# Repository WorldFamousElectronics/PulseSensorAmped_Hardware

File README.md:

# PulseSesorAmped_Hardware
These files were created in [Design Spark](http://www.designspark.com/) Schematic Layout and PCB Capture Software 

You will need to copy the contents of DesignSparkLibraryFiles into the default Library that Design Spark uses. Normally something like 

`Documents\DesignSpark PCB\Library`

This is the only way you will be able to use or modify the APDS-9008 part or the reverse mount LED part.

CONTRIBUTORS BACKTRACK AND NOTIFICATION

joel@pulsesensor.com
yury@pulsesensor.com

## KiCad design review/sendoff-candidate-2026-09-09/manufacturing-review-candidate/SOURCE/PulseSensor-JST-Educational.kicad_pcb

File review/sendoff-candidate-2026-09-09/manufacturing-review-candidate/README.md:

# PulseSensor JST educational board — review candidate

DEVELOPMENT • 2026-09-09 • PulseSilverBookPro

This is a concrete native CAD and manufacturing-export candidate, not an approved production release. No supplier upload or order has been made.

## Design

15.875 mm circular board, 1.6 mm thick. Black solder mask, white silkscreen on both sides. User-facing optical front is KiCad B side; circuit back is KiCad F side. D1, U1, J1 and board outline are unchanged. Twelve passive/diode parts were rearranged and copper rerouted; all original pin-to-net connections and local pad geometries are preserved.

The front uses a photo-reconstructed heart and curved pulsesensor.com wordmark. It is not verified against an original historical artwork master. Back lettering identifies parts and functional groups; dotted guides describe signal connections with deliberate gaps at crossings and text. They are explanatory ink, not a complete depiction of copper or current flow. The solid arrow describes conventional current on the LED cathode-to-resistor branch. Capacitors do not carry steady DC through their dielectric. The full component-function key is in the review page.

## Evidence

All 16 geometry/electrical comparison checks passed: zero unconnected nets, zero schematic parity issues, ERC clear, fixed optics preserved, correct 16-component placement export and unchanged controlled component selections. Native candidate SHA-256: 035ff099151d272f77bd0d54e158b8264b486bc1b7c166ecc0c92d3a766d4b6a.

DRC retains one original D1 optical NPTH / U1 courtyard exception. No new DRC warnings. Measured silk-to-opening clearance is at least 0.1536 mm on F and 0.1584 mm on B. Lettering targets 0.8 mm height and 0.15 mm strokes; full glyph stem metrology and supplier print reconciliation remain to be completed. See VALIDATION.

## Manufacturing review notes / hold points

- This package is on HOLD for release. Existing optical courtyard exception needs the formal review/waiver required by the hardware workflow.
- D1, D2 and U1 source models are mesh-only; verified STEP-capable models and independent mechanical inspection remain outstanding. Rendered component bodies are illustrative and do not constitute mechanical proof.
- Ten populated views are supplied. KiCad renders can display via holes/rings despite native tenting flags. Fabrication mask data and supplier tenting capability govern actual appearance; verify tenting for the 0.30 mm drills.
- Gerbers, drill and CPL share the original auxiliary origin (92.0625, 107.9375). CPL uses the native KiCad side/rotation convention. Confirm the supplier’s assembly interpretation before release.
- The controlled BOM and population matrix are byte-for-byte copies of the original submitted selections. Their original lot quantities/identifiers are provenance, not authorization for a new order. Reconcile the new lot explicitly before ordering.
- Human Gerber and assembly review, required repeat-build evidence, fabricator reconciliation and CEO release approval remain pending. This rearranged layout has not been bench validated.

## Provenance

Submitted source archive SHA-256: 0afda167b52ab0b0251cf22f91fd92fefa5dcf5e74f67b36446e7ec775acf792.
Submitted native PCB SHA-256: b439dcff82c4553731ac35ebcd27276899f8dfbbfcd35f2351d8101497eb4ad4.
Source: PulseSensor-Amped-B-PCBWay-EVT-RC3-R1-FINAL / SOURCE_SUPPORT / PulseSensor-Amped-B-JST.kicad_pcb.

Python crash dialogs were traced to KiCad pcbnew helper shutdown. Final metadata edits used standard Python text parsing and KiCad CLI checks/exports; the crash-prone helpers are no longer used.

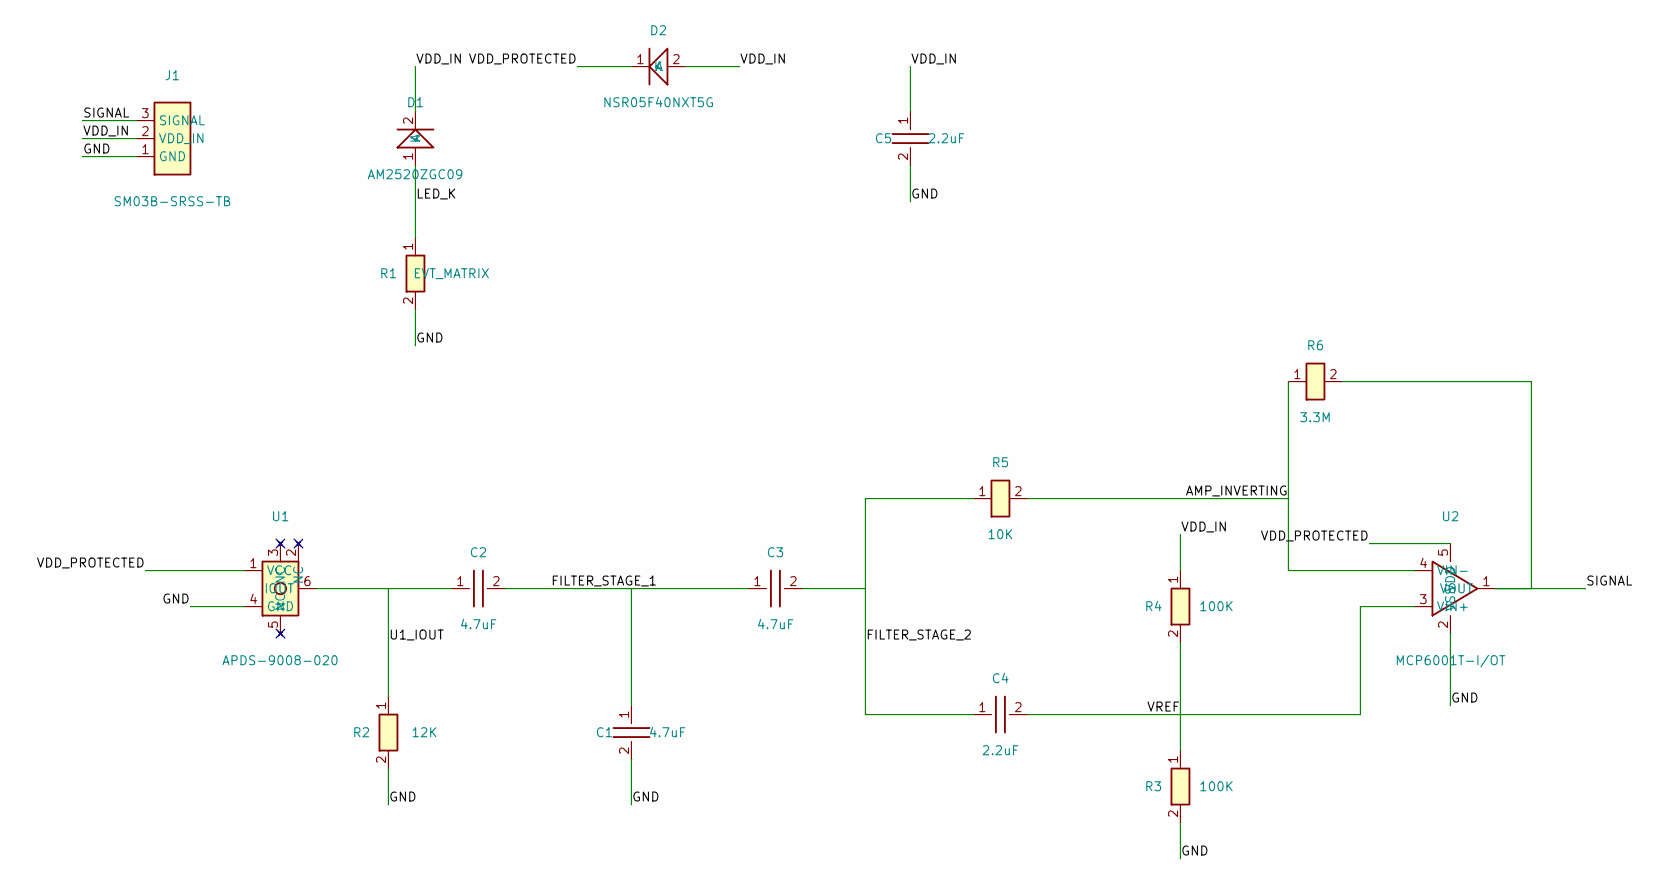
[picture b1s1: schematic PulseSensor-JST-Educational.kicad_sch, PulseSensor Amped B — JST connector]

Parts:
C1, C2, C3: 4.7uF; C_0402_Educational; MPN GRM155R60J475ME47D
C4, C5: 2.2uF; C_0402_Educational; MPN GRM155R61A225KE01D
D1: AM2520ZGC09; AM2520ZGC09_ReverseMount_OriginalAperture; MPN AM2520ZGC09
D2: NSR05F40NXT5G; NSR05F40NXT5G_DSN2; MPN NSR05F40NXT5G
J1: SM03B-SRSS-TB; JST_SH_SM03B-SRSS-TB_1x03-1MP_P1.00mm_Horizontal; MPN SM03B-SRSS-TB
R1: EVT_MATRIX; R_0402_Educational; MPN SEE_R1_SCREENING_MATRIX
R2: 12K; R_0402_Educational; MPN RC0402FR-0712KL
R3, R4: 100K; R_0402_Educational; MPN RC0402FR-07100KL
R5: 10K; R_0402_Educational; MPN RC0402FR-0710KL
R6: 3.3M; R_0402_Educational; MPN RC0402FR-073M3L
U1: APDS-9008-020; MPN APDS-9008-020
U2: MCP6001T-I/OT; SOT-23-5; MPN MCP6001T-I/OT

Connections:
/AMP_INVERTING: R5.2, R6.1, U2.4 (VIN-)
/FILTER_STAGE_1: C1.1, C2.2, C3.1
/FILTER_STAGE_2: C3.2, C4.1, R5.1
/GND: C1.2, C5.2, J1.1 (GND), R1.2, R2.2, R3.2, U1.4 (GND), U2.2 (VSS)
/LED_K: D1.1 (K), R1.1
/SIGNAL: J1.3 (SIGNAL), R6.2, U2.1 (VOUT)
/U1_IOUT: C2.1, R2.1, U1.6 (IOUT)
/VDD_IN: C5.1, D1.2 (A), D2.2 (A), J1.2 (VDD_IN), R4.1
/VDD_PROTECTED: D2.1 (K), U1.1 (VCC), U2.5 (VDD)
/VREF: C4.2, R3.1, R4.2, U2.3 (VIN+)

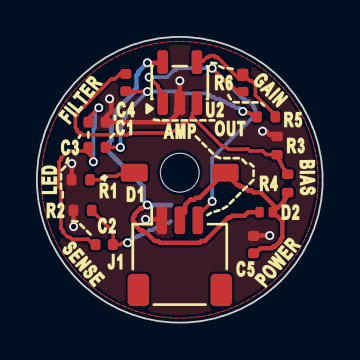
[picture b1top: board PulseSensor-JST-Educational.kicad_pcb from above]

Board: 2 copper layers, 15.9 x 15.9 mm, 16 parts (1 on the bottom side), 10 nets.

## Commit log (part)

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2016-07-27 Uploaded Hardware Design files
2017-08-30 Update License And Verify Files
2017-08-31 Updated .pcb file
    The previous .pcb file had extraneous text on it.
2018-02-27 Added Datasheet
2018-02-27 Added OSHWA Certification mark to datasheet
2025-12-01 Update gerber files in the Plots folder
    Somehow, the bottom layers were missing information. It's all there now.
2025-12-02 Replaced mistakenly removed files
